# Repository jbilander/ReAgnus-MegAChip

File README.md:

# ReAgnus-MegAChip
A ReAgnus MegaAChip PCB that takes a Gowin FPGA with embedded PSRAM, a PLCC-84 plug and FET level shifters.

***

THIS IS WORK IN PROGRESS, HARDWARE IS VERIFIED WORKING. FIRMWARE YET TO BE DEVELOPED. BUILD AT YOUR OWN RISK.

***

***

<br />

***

***

For hi-res pics goto the hi-res folder in pics
https://github.com/jbilander/ReAgnus-MegAChip/tree/main/pics/hi-res

***

BOM Rev. 2C
---------
Designator  | Name/Value   | Package | Notes
-|-|-|-|
U1 | Gowin FPGA GW1NR-UV9LQ144PC6/I5 | LQFP-144 | FPGA - Field Programmable Gate Array, 8640 LE, 121 I/O, Embedded 64Mbit 16-bit PSRAM <br /> [GW1NR-UV9LQ144PC6/I5](https://www.mouser.com/ProductDetail/192-1NRUV9LQ144PC6I5)
U2 | Voltage Regulator 3.3V, <br /> LM1117-3.3 or <br /> AMS1117-3.3 | SOT-223 | 3.3V 1A Low Drop-Out (LDO) Voltage regulator. https://www.aliexpress.com/item/32869037691.html
U3 | Voltage Regulator 4.3V, TPS73643DBVR or <br /> ABLIC S-1132B43-M5T1U | SOT-23-5 | 4.3V LDO Voltage Regulator<br />[TPS73643DBVR](https://www.mouser.com/ProductDetail/595-TPS73643DBVR) <br />[S-1132B43-M5T1U](https://www.mouser.com/ProductDetail/628-S-1132B43-M5T1G)
U4,U5,U6,U7 | Digital Bus Switch ICs 20-Bit FET, SN74CBT16210CDGVR | TVSOP-48 | FET Level-shifter <br /> [SN74CBT16210CDGVR](https://www.mouser.com/ProductDetail/595-SN74CBT16210CDGV)
U8 | 74LVC1G07 Single Buffer With Open-Drain Output | SOT-353, SC-70-5 | [74LVC1G07](https://www.mouser.com/ProductDetail/621-74LVC1G07SE-7)
U9 | X-tal driver 74LVC1GX04  | TSOP-6 1.65x3.05mm P0.95mm | [74LVC1GX04](https://www.mouser.com/ProductDetail/771-LVC1GX04GV125)
U10 | Bus Transceiver 74LVC245APW,118 | TSSOP-20 | [74LVC245APW-T](https://www.mouser.com/ProductDetail/771-74LVC245APW-T)
U11 | Voltage Regulator 1.8V, <br /> MCP1702T-1802E/CB | SOT-23 | 1.8V Low Drop-Out (LDO) Voltage regulator. [MCP1702T1802E-CB](https://www.mouser.com/ProductDetail/579-MCP1702T1802E-CB)
U12 | Winslow PLCC-84 Plug | PLCC-84 Plug | Optionally homemade plug
U13 | PLCC-84_TH_pin_holes | Agnus_TH_plug_pins | Pins to use with homemade plug, 1.27mm pitch Long Pin 1x40P or 1x50P [Aliexpress](https://www.aliexpress.com/item/32894911767.html) Cut to length after soldering.
Y1 | 18pF Crystal 28.6363 MHz (NTSC) or 28.375 MHz (PAL) | 3.2 mm x 2.5 mm | [ECS-286.3-18-33-JEM-TR](https://www.mouser.com/ProductDetail/520-286.3-18-33-JEMT) (NTSC)<br /> [ABM8-28.375MHZ-B2-T](https://www.mouser.com/ProductDetail/815-ABM8-28.375-B2-T) (PAL)
R1 | Resistor 1k Ω | 0603 | Resistor in optional Oscillator-circuit
R2 | Resistor 2.2M Ω | 0603 | Resistor in optional Oscillator-circuit
R3 | Resistor 33 Ω | 0603 | Series resistor for CLK from U9 to avoid reflections (in optional Oscillator-circuit).
R4 | Resistor 10k Ω | 0603 | Pull-up resistor for pin 41 (PAL/NTSC-selector for A500 Rev.6A/A2000/A3000-pinout) since A500 Rev.6A doesn't have pull-up on motherboard like A2000/A3000/A3000T have. Only needed for A500 Rev.6A. but doesn't hurt to populate anyway. 
R5 | Resistor 4.7k Ω | 0603 | Pull-down resistor for TCK in JTAG.
RN1 | 4.7k or 10k Ω RES ARRAY 4 Resistors | 1206 | [CAY16-4701F4LF](https://www.mouser.com/ProductDetail/652-CAY16A-4701F4LF) or [CAY16-103J4LF](https://www.mouser.com/ProductDetail/652-CAY16-103J4LF)
RN2 | 4.7k (CAY16-4701F4LF) RES ARRAY 4 Resistors | 1206 | [CAY16-4701F4LF](https://www.mouser.com/ProductDetail/652-CAY16A-4701F4LF)
C1 | Capacitor Radial Polarized 100uF | 2.5mm pitch, Through-Hole | [ECE-A0JKA101I](https://www.mouser.com/ProductDetail/667-ECE-A0JKA101I)
C2-C4 | Capacitor 10uF | 1206 | 
C5 | Capacitor 1uF | 0805 | 
C6 | Capacitor 10uF | 0805 |
C9 | Capacitor 1uF | 0805 |
C7,C8,C10-C16 | Capacitor 0.1uF = 100nF | 0805 |
C17-C19 | Capacitor 0.01uF = 10nF | 0805 (or 0603) |
C20 | Capacitor 0.1uF = 100nF | 0603 | Decoupling cap for U8
C21-C24 | Capacitor 0.1uF = 100nF | 0603 | Decoupling caps for U4-U7
C25 | Capacitor 0.1uF = 100nF | 0603 | Optional cap for U3, NR (Noise Reduction) pin 4 on TPS73643DBVR, this pin is NC on ABLIC S-1200B43-M5T1U
C26 | Capacitor 0.01uF = 10nF | 0603 |
C27-C28 | Capacitor 0.1uF = 100nF | 0603 |
C29-C30 | Multilayer Ceramic Capacitors MLCC - 32pF | 0603 | [06031A320FAT2A ](https://www.mouser.com/ProductDetail/581-06031A320FAT2A) Caps for optional oscillator circuit 
L1 | (Ferrite Bead 600ohms 100MHz .5A Monolithic) or 0 Ω resistor  | 0805 | [HZ0805E601R-10](https://www.mouser.com/ProductDetail/875-HZ0805E601R-10) or 0 Ω resistor 
J1 | VCC/GND Power Header Male | TH 1 x 2 Pin, 2.54mm pitch | For external power supply to allow programming of device when not plugged into the Amiga socket.
J2 | JTAG Pin Header Male | TH 2 x 5 Pin, 2.54mm pitch|
J3 | A20-A23 Pin Header Male | TH 2 x 2 Pin, 2.00mm pitch | Input Address lines for jumper-wires A20-A23
J4 | GND MountingHole_2.2mm_M2_Pad_Via | nut and bolt M2 size | for solid grounding via a ring lug connector and a thick jumper wire to Motherboard

***

Select one of the crystals 28.375 MHz (PAL) or 28.6363 MHz for the optional onboard oscillator circuit. Probably you want to select PAL/NTSC opposite to what your CLK on motherboard has, this in order to be able to switch between native PAL/NTSC with only a JP-setting on the MegaChip board.
***

***

***

***

***

***

***

***

***

***

***

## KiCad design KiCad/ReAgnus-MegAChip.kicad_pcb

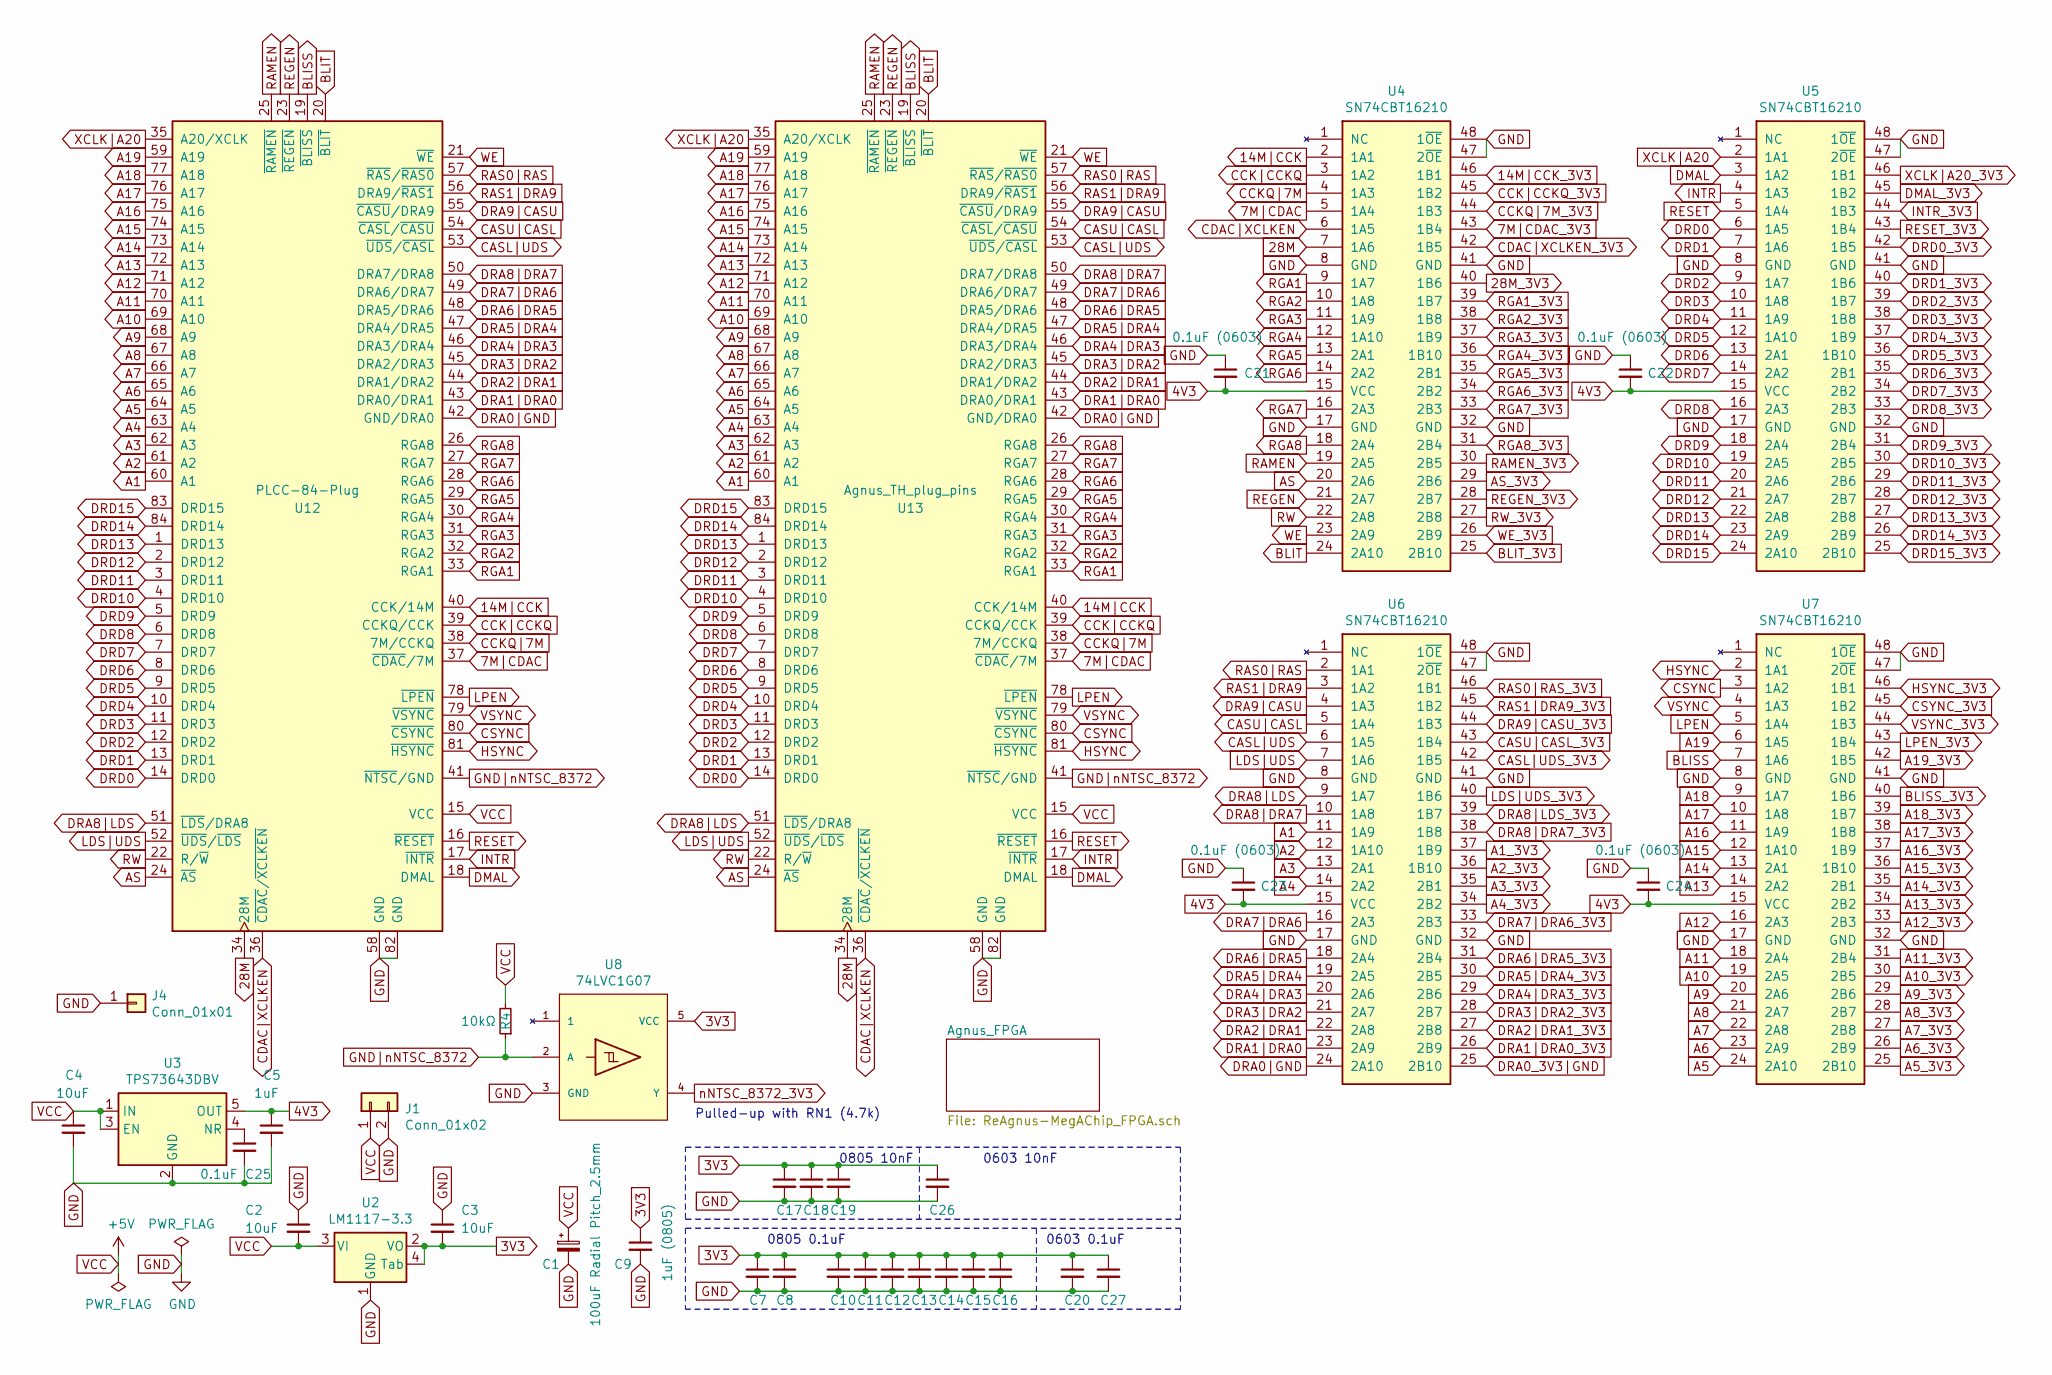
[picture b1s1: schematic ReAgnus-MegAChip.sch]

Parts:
C1: 100uF Radial Pitch_2.5mm; CP_Radial_D5.0mm_P2.50mm
C2, C3: 10uF; C_1206_3216Metric_Pad1.42x1.75mm_HandSolder
C4: 10uF; C_1206_3216Metric_Pad1.33x1.80mm_HandSolder
C5: 1uF; C_0805_2012Metric_Pad1.18x1.45mm_HandSolder
C7, C8, C10, C11, C12, C13, C14, C15, C16: 0.1uF; C_0805_2012Metric_Pad1.15x1.40mm_HandSolder
C9: 1uF (0805); C_0805_2012Metric_Pad1.15x1.40mm_HandSolder
C17, C18, C19: 0.01uF; C_0805_2012Metric_Pad1.15x1.40mm_HandSolder
C20, C26: 0.01uF; C_0603_1608Metric_Pad1.05x0.95mm_HandSolder
C21, C22, C23, C24: 0.1uF (0603); C_0603_1608Metric_Pad1.05x0.95mm_HandSolder
C25, C27: 0.1uF; C_0603_1608Metric_Pad1.08x0.95mm_HandSolder
J1: Conn_01x02; PinHeader_1x02_P2.54mm_Vertical
J4: Conn_01x01; MountingHole_2.2mm_M2_Pad_Via
R4: 10kΩ; R_0603_1608Metric_Pad0.98x0.95mm_HandSolder
U2: LM1117-3.3; SOT-223
U3: TPS73643DBV; SOT-23-5
U4, U5, U6, U7: SN74CBT16210; TSSOP-48_4.4x9.7mm_P0.4mm
U8: 74LVC1G07; SOT-353_SC-70-5_Custom_Handsoldering
U12: PLCC-84-Plug; PLCC-84_Plug_P1.27mm_mirrored
U13: Agnus_TH_plug_pins; PLCC-84_TH_pin_holes

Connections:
3V3: C3.2, C7.1, C8.1, C9.1, C10.1, C11.1, C12.1, C13.1, C14.1, C15.1, C16.1, C17.1, C18.1, C19.1, C20.1, C26.1, C27.1, U2.2 (VO), U2.4 (Tab), U8.5 (VCC); also elsewhere on the board
4V3: C5.1, C21.2, C22.2, C23.2, C24.2, U3.5 (OUT), U4.15 (VCC), U5.15 (VCC), U6.15 (VCC), U7.15 (VCC)
7M|CDAC: U4.5 (1A4), U12.37 (~CDAC~/7M), U13.37 (~CDAC~/7M)
7M|CDAC_3V3: U4.43 (1B4); also elsewhere on the board
14M|CCK: U4.2 (1A1), U12.40 (CCK/14M), U13.40 (CCK/14M)
14M|CCK_3V3: U4.46 (1B1); also elsewhere on the board
28M: U4.7 (1A6), U12.34 (28M), U13.34 (28M)
28M_3V3: U4.40 (1B6); also elsewhere on the board
A1: U6.11 (1A9), U12.60 (A1), U13.60 (A1)
A1_3V3: U6.37 (1B9); also elsewhere on the board
A2: U6.12 (1A10), U12.61 (A2), U13.61 (A2)
A2_3V3: U6.36 (1B10); also elsewhere on the board
A3: U6.13 (2A1), U12.62 (A3), U13.62 (A3)
A3_3V3: U6.35 (2B1); also elsewhere on the board
A4: U6.14 (2A2), U12.63 (A4), U13.63 (A4)
A4_3V3: U6.34 (2B2); also elsewhere on the board
A5: U7.24 (2A10), U12.64 (A5), U13.64 (A5)
A5_3V3: U7.25 (2B10); also elsewhere on the board
A6: U7.23 (2A9), U12.65 (A6), U13.65 (A6)
A6_3V3: U7.26 (2B9); also elsewhere on the board
A7: U7.22 (2A8), U12.66 (A7), U13.66 (A7)
A7_3V3: U7.27 (2B8); also elsewhere on the board
A8: U7.21 (2A7), U12.67 (A8), U13.67 (A8)
A8_3V3: U7.28 (2B7); also elsewhere on the board
A9: U7.20 (2A6), U12.68 (A9), U13.68 (A9)
A9_3V3: U7.29 (2B6); also elsewhere on the board
A10: U7.19 (2A5), U12.69 (A10), U13.69 (A10)
A10_3V3: U7.30 (2B5); also elsewhere on the board
A11: U7.18 (2A4), U12.70 (A11), U13.70 (A11)
A11_3V3: U7.31 (2B4); also elsewhere on the board
A12: U7.16 (2A3), U12.71 (A12), U13.71 (A12)
A12_3V3: U7.33 (2B3); also elsewhere on the board
A13: U7.14 (2A2), U12.72 (A13), U13.72 (A13)
A13_3V3: U7.34 (2B2); also elsewhere on the board
A14: U7.13 (2A1), U12.73 (A14), U13.73 (A14)
A14_3V3: U7.35 (2B1); also elsewhere on the board
A15: U7.12 (1A10), U12.74 (A15), U13.74 (A15)
A15_3V3: U7.36 (1B10); also elsewhere on the board
A16: U7.11 (1A9), U12.75 (A16), U13.75 (A16)
A16_3V3: U7.37 (1B9); also elsewhere on the board
A17: U7.10 (1A8), U12.76 (A17), U13.76 (A17)
A17_3V3: U7.38 (1B8); also elsewhere on the board
A18: U7.9 (1A7), U12.77 (A18), U13.77 (A18)
A18_3V3: U7.39 (1B7); also elsewhere on the board
A19: U7.6 (1A5), U12.59 (A19), U13.59 (A19)
A19_3V3: U7.42 (1B5); also elsewhere on the board
AS: U4.20 (2A6), U12.24 (~AS), U13.24 (~AS)
AS_3V3: U4.29 (2B6); also elsewhere on the board
BLISS: U7.7 (1A6), U12.19 (~BLISS), U13.19 (~BLISS)
BLISS_3V3: U7.40 (1B6); also elsewhere on the board
BLIT: U4.24 (2A10), U12.20 (~BLIT), U13.20 (~BLIT)
BLIT_3V3: U4.25 (2B10); also elsewhere on the board
CASL|UDS: U6.6 (1A5), U12.53 (~UDS~/~CASL), U13.53 (~UDS~/~CASL)
CASL|UDS_3V3: U6.42 (1B5); also elsewhere on the board
CASU|CASL: U6.5 (1A4), U12.54 (~CASL~/~CASU), U13.54 (~CASL~/~CASU)
CASU|CASL_3V3: U6.43 (1B4); also elsewhere on the board
CCKQ|7M: U4.4 (1A3), U12.38 (7M/CCKQ), U13.38 (7M/CCKQ)
CCKQ|7M_3V3: U4.44 (1B3); also elsewhere on the board
CCK|CCKQ: U4.3 (1A2), U12.39 (CCKQ/CCK), U13.39 (CCKQ/CCK)
CCK|CCKQ_3V3: U4.45 (1B2); also elsewhere on the board
CDAC|XCLKEN: U4.6 (1A5), U12.36 (~CDAC~/~XCLKEN), U13.36 (~CDAC~/~XCLKEN)
CDAC|XCLKEN_3V3: U4.42 (1B5); also elsewhere on the board
CSYNC: U7.3 (1A2), U12.80 (~CSYNC), U13.80 (~CSYNC)
CSYNC_3V3: U7.45 (1B2); also elsewhere on the board
DMAL: U5.3 (1A2), U12.18 (DMAL), U13.18 (DMAL)
DMAL_3V3: U5.45 (1B2); also elsewhere on the board
DRA0_3V3|GND: U6.25 (2B10); also elsewhere on the board
DRA0|GND: U6.24 (2A10), U12.42 (GND/DRA0), U13.42 (GND/DRA0)
DRA1|DRA0: U6.23 (2A9), U12.43 (DRA0/DRA1), U13.43 (DRA0/DRA1)
DRA1|DRA0_3V3: U6.26 (2B9); also elsewhere on the board
DRA2|DRA1: U6.22 (2A8), U12.44 (DRA1/DRA2), U13.44 (DRA1/DRA2)
DRA2|DRA1_3V3: U6.27 (2B8); also elsewhere on the board
DRA3|DRA2: U6.21 (2A7), U12.45 (DRA2/DRA3), U13.45 (DRA2/DRA3)
DRA3|DRA2_3V3: U6.28 (2B7); also elsewhere on the board
DRA4|DRA3: U6.20 (2A6), U12.46 (DRA3/DRA4), U13.46 (DRA3/DRA4)
DRA4|DRA3_3V3: U6.29 (2B6); also elsewhere on the board
DRA5|DRA4: U6.19 (2A5), U12.47 (DRA4/DRA5), U13.47 (DRA4/DRA5)
DRA5|DRA4_3V3: U6.30 (2B5); also elsewhere on the board
DRA6|DRA5: U6.18 (2A4), U12.48 (DRA5/DRA6), U13.48 (DRA5/DRA6)
DRA6|DRA5_3V3: U6.31 (2B4); also elsewhere on the board
DRA7|DRA6: U6.16 (2A3), U12.49 (DRA6/DRA7), U13.49 (DRA6/DRA7)
DRA7|DRA6_3V3: U6.33 (2B3); also elsewhere on the board
DRA8|DRA7: U6.10 (1A8), U12.50 (DRA7/DRA8), U13.50 (DRA7/DRA8)
DRA8|DRA7_3V3: U6.38 (1B8); also elsewhere on the board
DRA8|LDS: U6.9 (1A7), U12.51 (~LDS~/DRA8), U13.51 (~LDS~/DRA8)
DRA8|LDS_3V3: U6.39 (1B7); also elsewhere on the board
DRA9|CASU: U6.4 (1A3), U12.55 (~CASU~/DRA9), U13.55 (~CASU~/DRA9)
DRA9|CASU_3V3: U6.44 (1B3); also elsewhere on the board
DRD0: U5.6 (1A5), U12.14 (DRD0), U13.14 (DRD0)
DRD0_3V3: U5.42 (1B5); also elsewhere on the board
DRD1: U5.7 (1A6), U12.13 (DRD1), U13.13 (DRD1)
DRD1_3V3: U5.40 (1B6); also elsewhere on the board
DRD2: U5.9 (1A7), U12.12 (DRD2), U13.12 (DRD2)
DRD2_3V3: U5.39 (1B7); also elsewhere on the board
DRD3: U5.10 (1A8), U12.11 (DRD3), U13.11 (DRD3)
DRD3_3V3: U5.38 (1B8); also elsewhere on the board
DRD4: U5.11 (1A9), U12.10 (DRD4), U13.10 (DRD4)
DRD4_3V3: U5.37 (1B9); also elsewhere on the board
DRD5: U5.12 (1A10), U12.9 (DRD5), U13.9 (DRD5)
DRD5_3V3: U5.36 (1B10); also elsewhere on the board
DRD6: U5.13 (2A1), U12.8 (DRD6), U13.8 (DRD6)
DRD6_3V3: U5.35 (2B1); also elsewhere on the board
DRD7: U5.14 (2A2), U12.7 (DRD7), U13.7 (DRD7)
DRD7_3V3: U5.34 (2B2); also elsewhere on the board
DRD8: U5.16 (2A3), U12.6 (DRD8), U13.6 (DRD8)
DRD8_3V3: U5.33 (2B3); also elsewhere on the board
DRD9: U5.18 (2A4), U12.5 (DRD9), U13.5 (DRD9)
DRD9_3V3: U5.31 (2B4); also elsewhere on the board
DRD10: U5.19 (2A5), U12.4 (DRD10), U13.4 (DRD10)
DRD10_3V3: U5.30 (2B5); also elsewhere on the board
DRD11: U5.20 (2A6), U12.3 (DRD11), U13.3 (DRD11)
DRD11_3V3: U5.29 (2B6); also elsewhere on the board
DRD12: U5.21 (2A7), U12.2 (DRD12), U13.2 (DRD12)
DRD12_3V3: U5.28 (2B7); also elsewhere on the board
DRD13: U5.22 (2A8), U12.1 (DRD13), U13.1 (DRD13)
DRD13_3V3: U5.27 (2B8); also elsewhere on the board
DRD14: U5.23 (2A9), U12.84 (DRD14), U13.84 (DRD14)
DRD14_3V3: U5.26 (2B9); also elsewhere on the board
DRD15: U5.24 (2A10), U12.83 (DRD15), U13.83 (DRD15)
DRD15_3V3: U5.25 (2B10); also elsewhere on the board
GND: C1.2, C2.1, C3.1, C4.2, C5.2, C7.2, C8.2, C9.2, C10.2, C11.2, C12.2, C13.2, C14.2, C15.2, C16.2, C17.2, C18.2, C19.2, C20.2, C21.1, C22.1, C23.1, C24.1, C25.2, C26.2, C27.2, J1.2, J4.1, U2.1 (GND), U3.2 (GND), U4.8 (GND), U4.17 (GND), U4.32 (GND), U4.41 (GND), U4.47 (2~OE), U4.48 (1~OE), U5.8 (GND), U5.17 (GND), U5.32 (GND), U5.41 (GND), U5.47 (2~OE), U5.48 (1~OE), U6.8 (GND), U6.17 (GND), U6.32 (GND), U6.41 (GND), U6.47 (2~OE), U6.48 (1~OE), U7.8 (GND), U7.17 (GND), U7.32 (GND), U7.41 (GND), U7.47 (2~OE), U7.48 (1~OE), U8.3 (GND), U12.58 (GND), U12.82 (GND), U13.58 (GND), U13.82 (GND); also elsewhere on the board
GND|nNTSC_8372: R4.1, U8.2 (A), U12.41 (~NTSC~/GND), U13.41 (~NTSC~/GND)
HSYNC: U7.2 (1A1), U12.81 (~HSYNC), U13.81 (~HSYNC)
HSYNC_3V3: U7.46 (1B1); also elsewhere on the board
INTR: U5.4 (1A3), U12.17 (~INTR), U13.17 (~INTR)
INTR_3V3: U5.44 (1B3); also elsewhere on the board
LDS|UDS: U6.7 (1A6), U12.52 (~UDS~/~LDS~), U13.52 (~UDS~/~LDS~)
LDS|UDS_3V3: U6.40 (1B6); also elsewhere on the board
LPEN: U7.5 (1A4), U12.78 (~LPEN), U13.78 (~LPEN)
LPEN_3V3: U7.43 (1B4); also elsewhere on the board
unnamed: C25.1, U3.4 (NR)
RAMEN: U4.19 (2A5), U12.25 (~RAMEN), U13.25 (~RAMEN)
RAMEN_3V3: U4.30 (2B5); also elsewhere on the board
RAS0|RAS: U6.2 (1A1), U12.57 (~RAS~/~RAS0), U13.57 (~RAS~/~RAS0)
RAS0|RAS_3V3: U6.46 (1B1); also elsewhere on the board
RAS1|DRA9: U6.3 (1A2), U12.56 (DRA9/~RAS1), U13.56 (DRA9/~RAS1)
RAS1|DRA9_3V3: U6.45 (1B2); also elsewhere on the board
REGEN: U4.21 (2A7), U12.23 (~REGEN), U13.23 (~REGEN)
REGEN_3V3: U4.28 (2B7); also elsewhere on the board
RESET: U5.5 (1A4), U12.16 (~RESET), U13.16 (~RESET)
RESET_3V3: U5.43 (1B4); also elsewhere on the board
RGA1: U4.9 (1A7), U12.33 (RGA1), U13.33 (RGA1)
RGA1_3V3: U4.39 (1B7); also elsewhere on the board
RGA2: U4.10 (1A8), U12.32 (RGA2), U13.32 (RGA2)
RGA2_3V3: U4.38 (1B8); also elsewhere on the board
RGA3: U4.11 (1A9), U12.31 (RGA3), U13.31 (RGA3)
RGA3_3V3: U4.37 (1B9); also elsewhere on the board
RGA4: U4.12 (1A10), U12.30 (RGA4), U13.30 (RGA4)
RGA4_3V3: U4.36 (1B10); also elsewhere on the board
RGA5: U4.13 (2A1), U12.29 (RGA5), U13.29 (RGA5)
RGA5_3V3: U4.35 (2B1); also elsewhere on the board
RGA6: U4.14 (2A2), U12.28 (RGA6), U13.28 (RGA6)
RGA6_3V3: U4.34 (2B2); also elsewhere on the board
RGA7: U4.16 (2A3), U12.27 (RGA7), U13.27 (RGA7)
RGA7_3V3: U4.33 (2B3); also elsewhere on the board
RGA8: U4.18 (2A4), U12.26 (RGA8), U13.26 (RGA8)
RGA8_3V3: U4.31 (2B4); also elsewhere on the board
RW: U4.22 (2A8), U12.22 (R/~W), U13.22 (R/~W)
RW_3V3: U4.27 (2B8); also elsewhere on the board
VCC: C1.1, C2.2, C4.1, J1.1, R4.2, U2.3 (VI), U3.1 (IN), U3.3 (EN), U12.15 (VCC), U13.15 (VCC)
VSYNC: U7.4 (1A3), U12.79 (~VSYNC), U13.79 (~VSYNC)
VSYNC_3V3: U7.44 (1B3); also elsewhere on the board
WE: U4.23 (2A9), U12.21 (~WE), U13.21 (~WE)
WE_3V3: U4.26 (2B9); also elsewhere on the board
XCLK|A20: U5.2 (1A1), U12.35 (A20/XCLK), U13.35 (A20/XCLK)
XCLK|A20_3V3: U5.46 (1B1); also elsewhere on the board
nNTSC_8372_3V3: U8.4 (Y); also elsewhere on the board

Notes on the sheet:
Pulled-up with RN1 (4.7k)
0805 10nF
0805 0.1uF
0603 10nF
0603 0.1uF

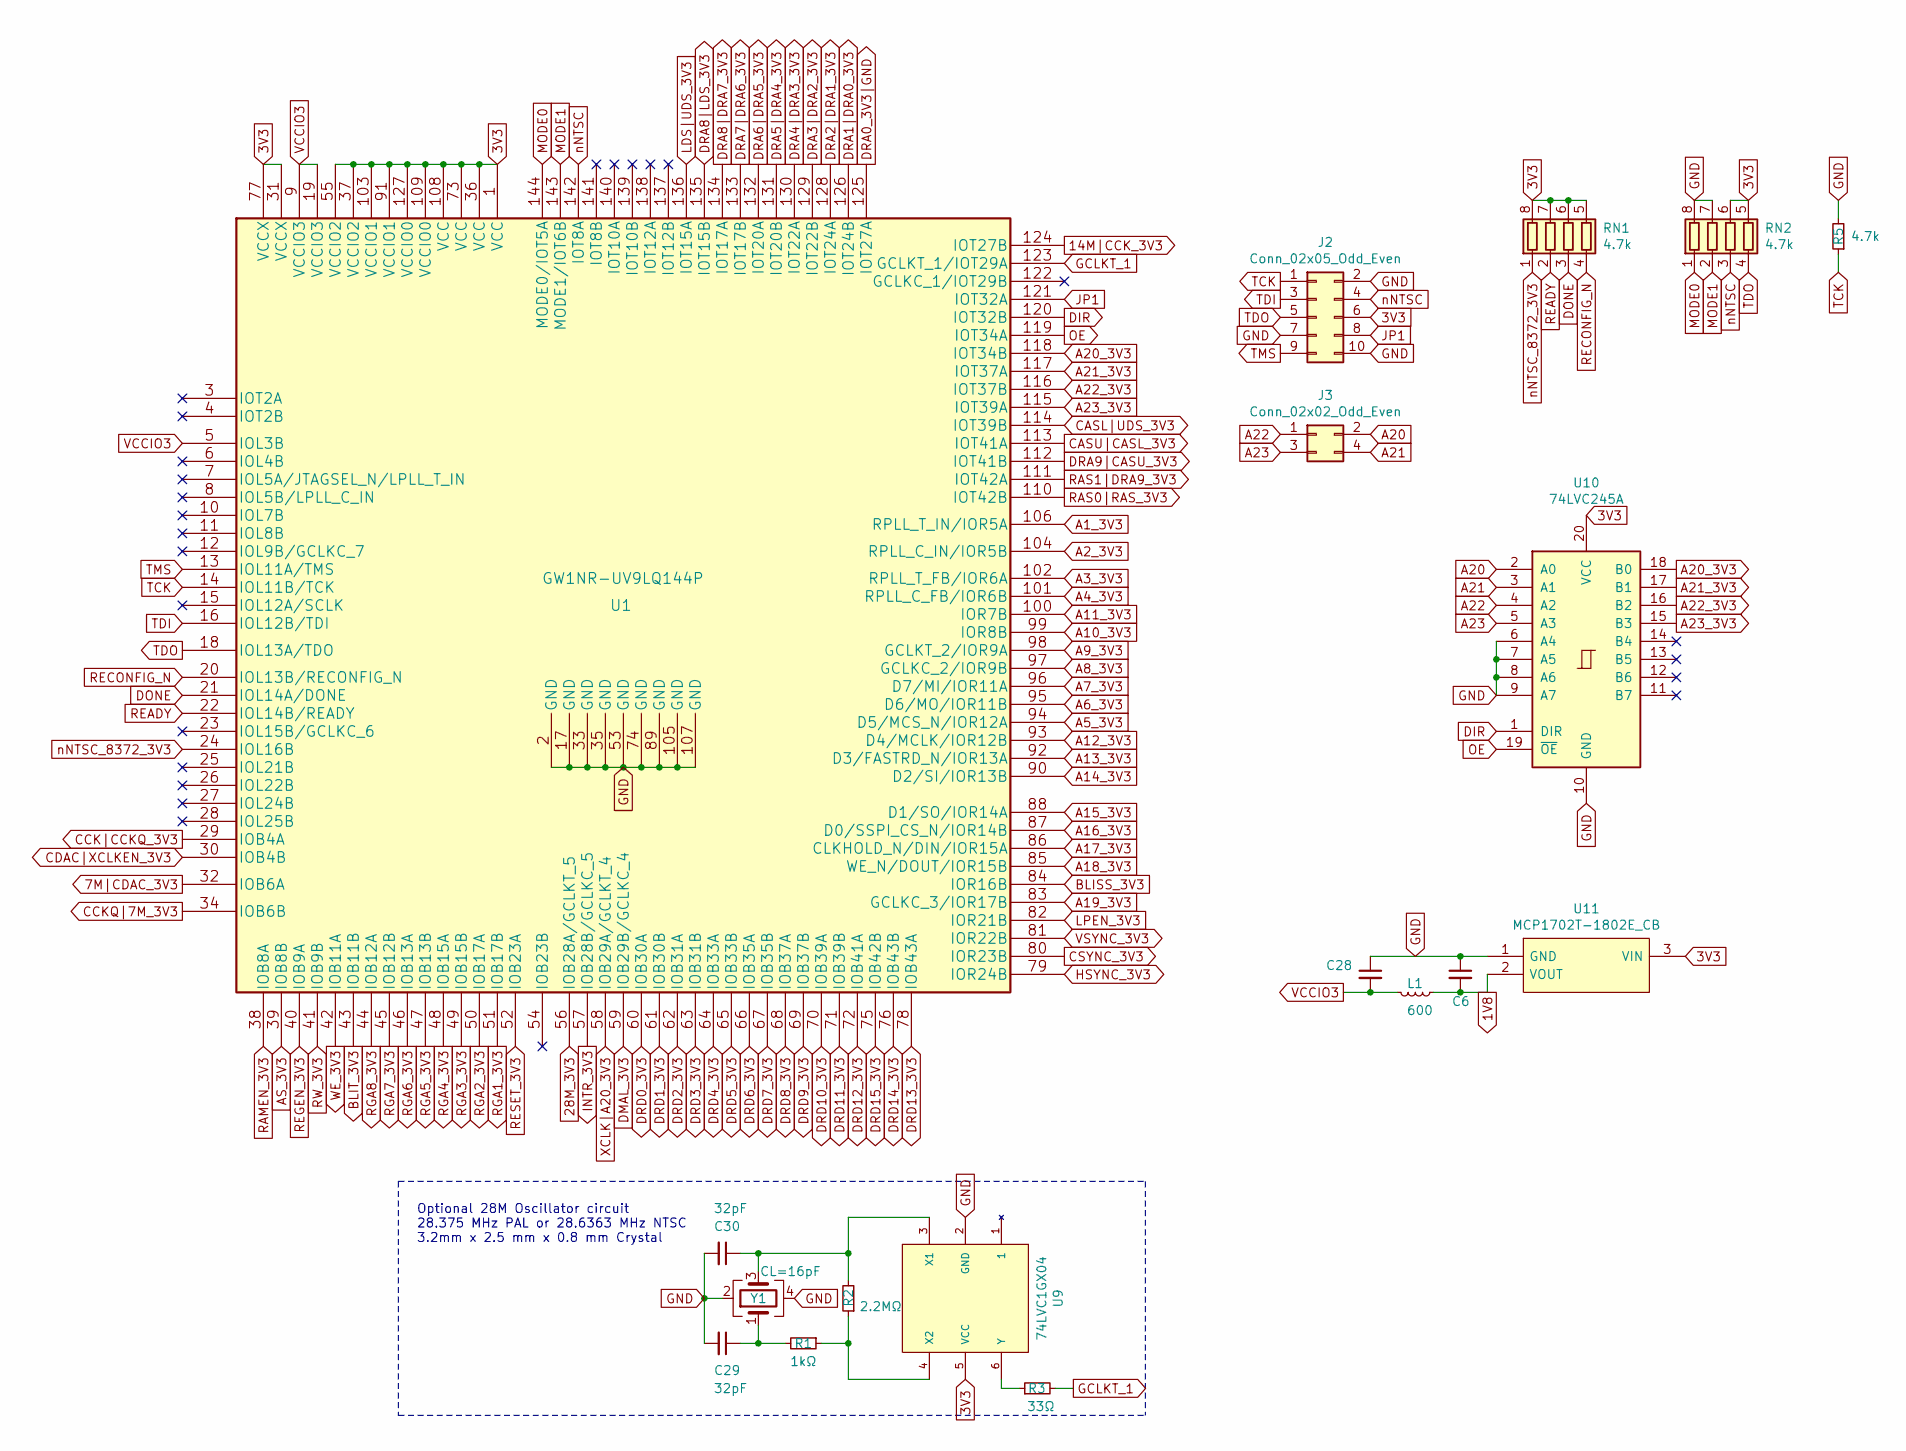
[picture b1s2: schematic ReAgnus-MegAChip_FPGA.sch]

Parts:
C6: 10uF; C_0805_2012Metric_Pad1.18x1.45mm_HandSolder
C28: 0.1uF; C_0603_1608Metric_Pad1.08x0.95mm_HandSolder
C29, C30: 32pF; C_0603_1608Metric_Pad1.05x0.95mm_HandSolder
J2: Conn_02x05_Odd_Even; PinHeader_2x05_P2.54mm_Vertical
J3: Conn_02x02_Odd_Even; PinHeader_2x02_P2.00mm_Vertical
L1: 600; L_0805_2012Metric_Pad1.05x1.20mm_HandSolder
R1: 1kΩ; R_0603_1608Metric_Pad1.05x0.95mm_HandSolder
R2: 2.2MΩ; R_0603_1608Metric_Pad1.05x0.95mm_HandSolder
R3: 33Ω; R_0603_1608Metric_Pad0.98x0.95mm_HandSolder
R5: 4.7k; R_0603_1608Metric_Pad0.98x0.95mm_HandSolder
RN1, RN2: 4.7k; RESCAF80P320X160X60-8N
U1: GW1NR-UV9LQ144P; LQFP-144_20x20mm_P0.5mm
U9: 74LVC1GX04; TSOP-6_1.65x3.05mm_P0.95mm
U10: 74LVC245A; TSSOP-20_4.4x6.5mm_P0.65mm
U11: MCP1702T-1802E_CB; SOT-23_Handsoldering
Y1: CL=16pF; Crystal_SMD_SeikoEpson_FA238-4Pin_3.2x2.5mm

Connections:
1V8: C6.2, L1.1, U11.2 (VOUT)
3V3: J2.6, RN1.5 (R4.2), RN1.6 (R3.2), RN1.7 (R2.2), RN1.8 (R1.2), RN2.5 (R4.2), RN2.6 (R3.2), U1.1 (VCC), U1.31 (VCCX), U1.36 (VCC), U1.37 (VCCIO2), U1.55 (VCCIO2), U1.73 (VCC), U1.77 (VCCX), U1.91 (VCCIO1), U1.103 (VCCIO1), U1.108 (VCC), U1.109 (VCCIO0), U1.127 (VCCIO0), U9.5 (VCC), U10.20 (VCC), U11.3 (VIN); also elsewhere on the board
7M|CDAC_3V3: U1.32 (IOB6A); also elsewhere on the board
14M|CCK_3V3: U1.124 (IOT27B); also elsewhere on the board
28M_3V3: U1.56 (IOB28A/GCLKT_5); also elsewhere on the board
A1_3V3: U1.106 (RPLL_T_IN/IOR5A); also elsewhere on the board
A2_3V3: U1.104 (RPLL_C_IN/IOR5B); also elsewhere on the board
A3_3V3: U1.102 (RPLL_T_FB/IOR6A); also elsewhere on the board
A4_3V3: U1.101 (RPLL_C_FB/IOR6B); also elsewhere on the board
A5_3V3: U1.94 (D5/MCS_N/IOR12A); also elsewhere on the board
A6_3V3: U1.95 (D6/MO/IOR11B); also elsewhere on the board
A7_3V3: U1.96 (D7/MI/IOR11A); also elsewhere on the board
A8_3V3: U1.97 (GCLKC_2/IOR9B); also elsewhere on the board
A9_3V3: U1.98 (GCLKT_2/IOR9A); also elsewhere on the board
A10_3V3: U1.99 (IOR8B); also elsewhere on the board
A11_3V3: U1.100 (IOR7B); also elsewhere on the board
A12_3V3: U1.93 (D4/MCLK/IOR12B); also elsewhere on the board
A13_3V3: U1.92 (D3/FASTRD_N/IOR13A); also elsewhere on the board
A14_3V3: U1.90 (D2/SI/IOR13B); also elsewhere on the board
A15_3V3: U1.88 (D1/SO/IOR14A); also elsewhere on the board
A16_3V3: U1.87 (D0/SSPI_CS_N/IOR14B); also elsewhere on the board
A17_3V3: U1.86 (CLKHOLD_N/DIN/IOR15A); also elsewhere on the board
A18_3V3: U1.85 (WE_N/DOUT/IOR15B); also elsewhere on the board
A19_3V3: U1.83 (GCLKC_3/IOR17B); also elsewhere on the board
A20: J3.2, U10.2 (A0)
A20_3V3: U1.118 (IOT34B), U10.18 (B0)
A21: J3.4, U10.3 (A1)
A21_3V3: U1.117 (IOT37A), U10.17 (B1)
A22: J3.1, U10.4 (A2)
A22_3V3: U1.116 (IOT37B), U10.16 (B2)
A23: J3.3, U10.5 (A3)
A23_3V3: U1.115 (IOT39A), U10.15 (B3)
AS_3V3: U1.39 (IOB8B); also elsewhere on the board
BLISS_3V3: U1.84 (IOR16B); also elsewhere on the board
BLIT_3V3: U1.43 (IOB11B); also elsewhere on the board
CASL|UDS_3V3: U1.114 (IOT39B); also elsewhere on the board
CASU|CASL_3V3: U1.113 (IOT41A); also elsewhere on the board
CCKQ|7M_3V3: U1.34 (IOB6B); also elsewhere on the board
CCK|CCKQ_3V3: U1.29 (IOB4A); also elsewhere on the board
CDAC|XCLKEN_3V3: U1.30 (IOB4B); also elsewhere on the board
CSYNC_3V3: U1.80 (IOR23B); also elsewhere on the board
DIR: U1.120 (IOT32B), U10.1 (DIR)
DMAL_3V3: U1.59 (IOB29B/GCLKC_4); also elsewhere on the board
DONE: RN1.3 (R3.1), U1.21 (IOL14A/DONE)
DRA0_3V3|GND: U1.125 (IOT27A); also elsewhere on the board
DRA1|DRA0_3V3: U1.126 (IOT24B); also elsewhere on the board
DRA2|DRA1_3V3: U1.128 (IOT24A); also elsewhere on the board
DRA3|DRA2_3V3: U1.129 (IOT22B); also elsewhere on the board
DRA4|DRA3_3V3: U1.130 (IOT22A); also elsewhere on the board
DRA5|DRA4_3V3: U1.131 (IOT20B); also elsewhere on the board
DRA6|DRA5_3V3: U1.132 (IOT20A); also elsewhere on the board
DRA7|DRA6_3V3: U1.133 (IOT17B); also elsewhere on the board
DRA8|DRA7_3V3: U1.134 (IOT17A); also elsewhere on the board
DRA8|LDS_3V3: U1.135 (IOT15B); also elsewhere on the board
DRA9|CASU_3V3: U1.112 (IOT41B); also elsewhere on the board
DRD0_3V3: U1.60 (IOB30A); also elsewhere on the board
DRD1_3V3: U1.61 (IOB30B); also elsewhere on the board
DRD2_3V3: U1.62 (IOB31A); also elsewhere on the board
DRD3_3V3: U1.63 (IOB31B); also elsewhere on the board
DRD4_3V3: U1.64 (IOB33A); also elsewhere on the board
DRD5_3V3: U1.65 (IOB33B); also elsewhere on the board
DRD6_3V3: U1.66 (IOB35A); also elsewhere on the board
DRD7_3V3: U1.67 (IOB35B); also elsewhere on the board
DRD8_3V3: U1.68 (IOB37A); also elsewhere on the board
DRD9_3V3: U1.69 (IOB37B); also elsewhere on the board
DRD10_3V3: U1.70 (IOB39A); also elsewhere on the board
DRD11_3V3: U1.71 (IOB39B); also elsewhere on the board
DRD12_3V3: U1.72 (IOB41A); also elsewhere on the board
DRD13_3V3: U1.78 (IOB43A); also elsewhere on the board
DRD14_3V3: U1.76 (IOB43B); also elsewhere on the board
DRD15_3V3: U1.75 (IOB42B); also elsewhere on the board
GCLKT_1: R3.2, U1.123 (GCLKT_1/IOT29A)
GND: C6.1, C28.1, C29.2, C30.2, J2.2, J2.7, J2.10, R5.2, RN2.7 (R2.2), RN2.8 (R1.2), U1.2 (GND), U1.17 (GND), U1.33 (GND), U1.35 (GND), U1.53 (GND), U1.74 (GND), U1.89 (GND), U1.105 (GND), U1.107 (GND), U9.2 (GND), U10.6 (A4), U10.7 (A5), U10.8 (A6), U10.9 (A7), U10.10 (GND), U11.1 (GND), Y1.2, Y1.4; also elsewhere on the board
HSYNC_3V3: U1.79 (IOR24B); also elsewhere on the board
INTR_3V3: U1.57 (IOB28B/GCLKC_5); also elsewhere on the board
JP1: J2.8, U1.121 (IOT32A)
LDS|UDS_3V3: U1.136 (IOT15A); also elsewhere on the board
LPEN_3V3: U1.82 (IOR21B); also elsewhere on the board
MODE0: RN2.1 (R1.1), U1.144 (MODE0/IOT5A)
MODE1: RN2.2 (R2.1), U1.143 (MODE1/IOT6B)
unnamed: C29.1, R1.2, Y1.1
unnamed: C30.1, R2.2, U9.3 (X1), Y1.3
unnamed: R1.1, R2.1, U9.4 (X2)
unnamed: R3.1, U9.6 (Y)
OE: U1.119 (IOT34A), U10.19 (~OE)
RAMEN_3V3: U1.38 (IOB8A); also elsewhere on the board
RAS0|RAS_3V3: U1.110 (IOT42B); also elsewhere on the board
RAS1|DRA9_3V3: U1.111 (IOT42A); also elsewhere on the board
READY: RN1.2 (R2.1), U1.22 (IOL14B/READY)
RECONFIG_N: RN1.4 (R4.1), U1.20 (IOL13B/RECONFIG_N)
REGEN_3V3: U1.40 (IOB9A); also elsewhere on the board
RESET_3V3: U1.52 (IOB23A); also elsewhere on the board
RGA1_3V3: U1.51 (IOB17B); also elsewhere on the board
RGA2_3V3: U1.50 (IOB17A); also elsewhere on the board
RGA3_3V3: U1.49 (IOB15B); also elsewhere on the board
RGA4_3V3: U1.48 (IOB15A); also elsewhere on the board
RGA5_3V3: U1.47 (IOB13B); also elsewhere on the board
RGA6_3V3: U1.46 (IOB13A); also elsewhere on the board
RGA7_3V3: U1.45 (IOB12B); also elsewhere on the board
RGA8_3V3: U1.44 (IOB12A); also elsewhere on the board
RW_3V3: U1.41 (IOB9B); also elsewhere on the board
TCK: J2.1, R5.1, U1.14 (IOL11B/TCK)
TDI: J2.3, U1.16 (IOL12B/TDI)
TDO: J2.5, RN2.4 (R4.1), U1.18 (IOL13A/TDO)
TMS: J2.9, U1.13 (IOL11A/TMS)
VCCIO3: C28.2, L1.2, U1.5 (IOL3B), U1.9 (VCCIO3), U1.19 (VCCIO3)
VSYNC_3V3: U1.81 (IOR22B); also elsewhere on the board
WE_3V3: U1.42 (IOB11A); also elsewhere on the board
XCLK|A20_3V3: U1.58 (IOB29A/GCLKT_4); also elsewhere on the board
nNTSC: J2.4, RN2.3 (R3.1), U1.142 (IOT8A)
nNTSC_8372_3V3: RN1.1 (R1.1), U1.24 (IOL16B); also elsewhere on the board

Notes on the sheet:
Optional 28M Oscillator circuit 28.375 MHz PAL or 28.6363 MHz NTSC 3.2mm x 2.5 mm x 0.8 mm Crystal

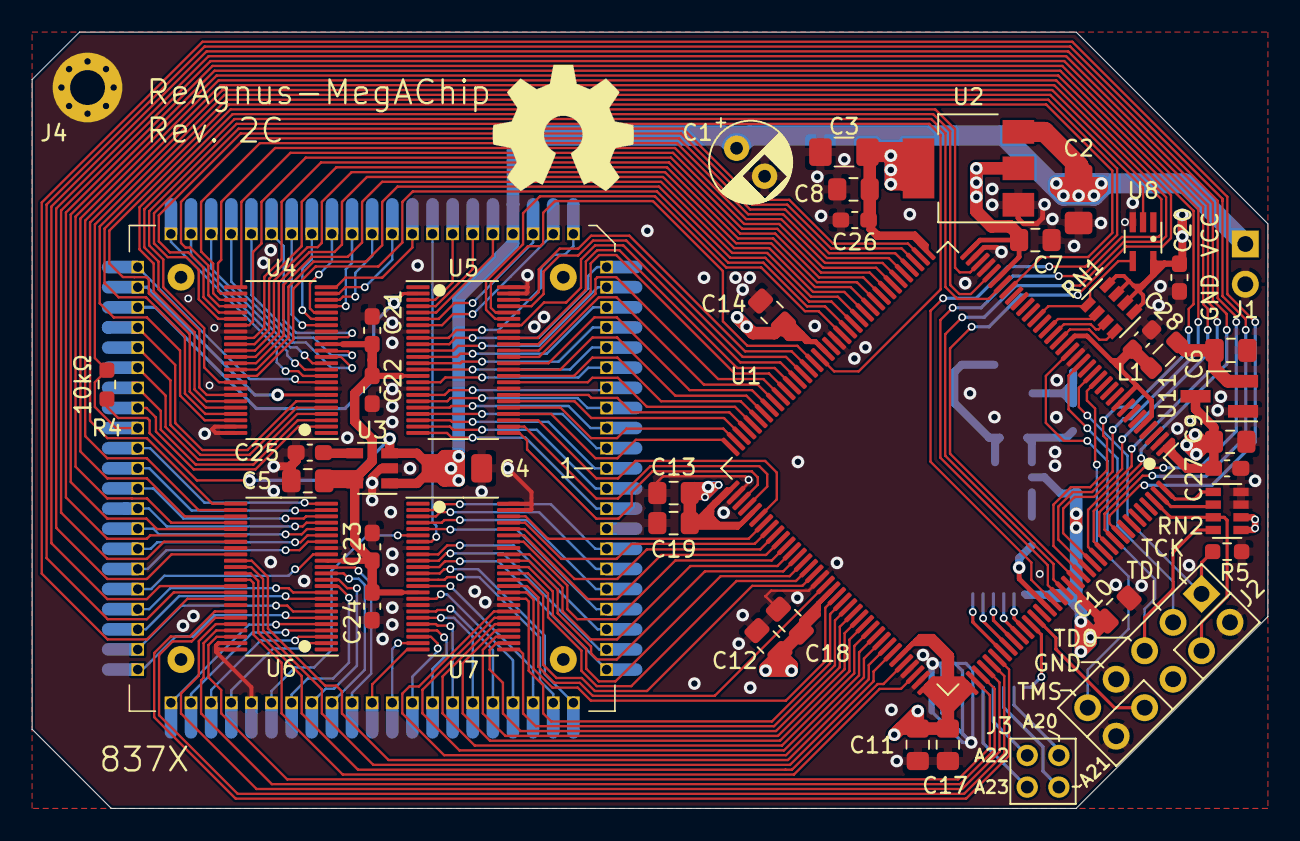
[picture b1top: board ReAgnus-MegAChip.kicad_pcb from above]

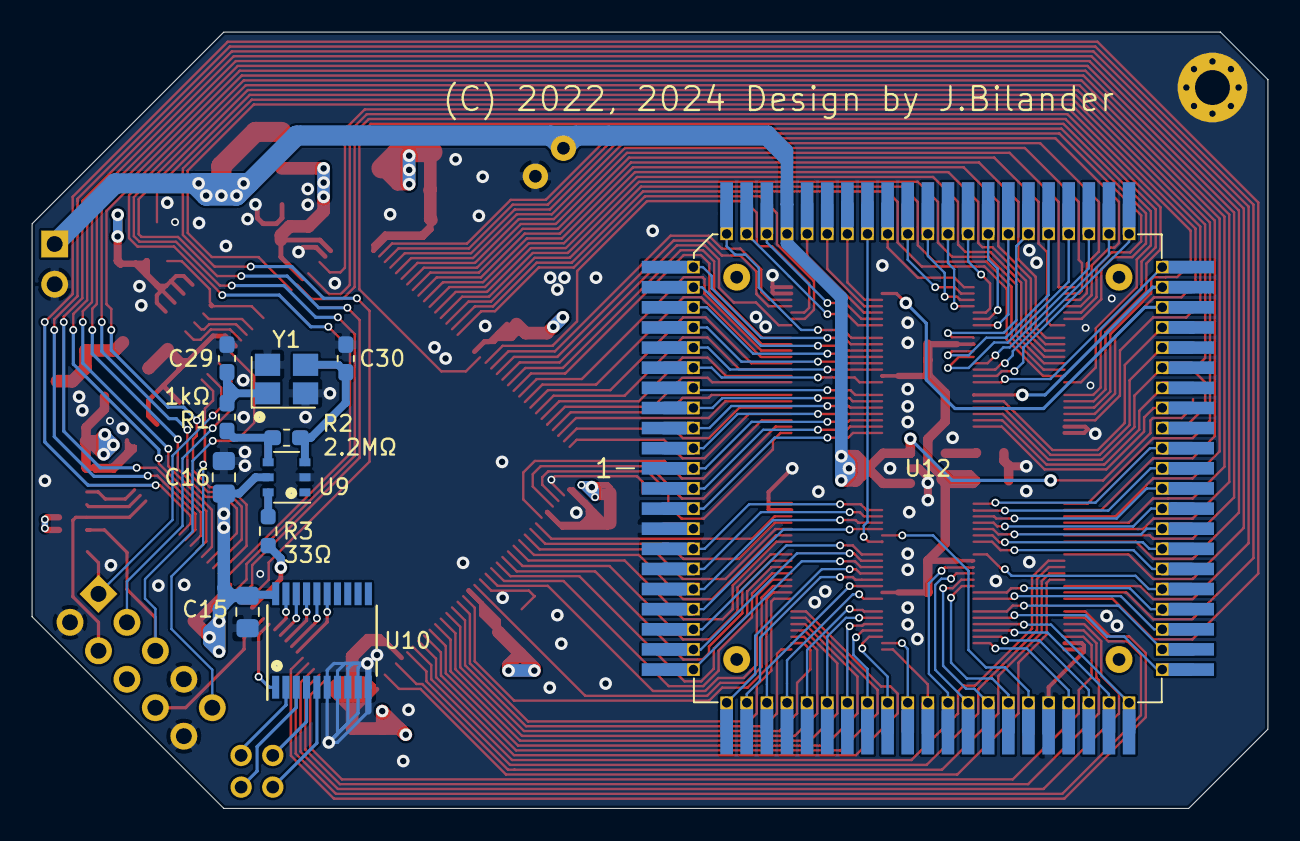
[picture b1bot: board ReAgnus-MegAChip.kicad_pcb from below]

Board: 4 copper layers, 78.0 x 49.0 mm, 56 parts (11 on the bottom side), 195 nets.

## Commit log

2022-08-22 Create LICENSE
2022-08-22 added KiCAD files
2022-08-26 added FPGA schematic file
2022-08-26 more routing and placing components
2022-08-28 made custom footprint
2022-09-01 commit before PCB design change
2022-09-01 major redesign of PCB done
2022-09-02 added footprint
2022-09-02 added 74LVC1G07 buffer with open-drain output
2022-09-03 more routing
2022-09-03 added pull-up resistors on PAL/NTSC-line, added JTAG-header
2022-09-07 fixed routing for VCC to voltage regulator, placed two-pin header for VCC/GND and more routing
2022-09-08 added 3D step file for cay16-103j4lf resistor pack
2022-09-08 went to two layers, deleted inner layers GND and VCC
2022-09-09 renaming of Capacitors
2022-09-14 added Oscillator X1 for SDRAM and GCLKT_1 pin on FPGA
2022-09-15 added 74LVC245A
2022-09-15 added 74LVC245A IC for A20-A23 and more routing done
2022-09-16 added 74LVC1GX04 X-tal driver
2022-09-17 corrected X2-pin to an output on 74LVC1GX04-symbol
2022-09-17 added optional Oscillator circuit with 28M crystal 3.2mm x 2.5mm x 0.8mm
2022-09-22 silkscreen fixes
2022-09-23 added decoupling cap for U11
2022-09-23 fixed power routing and decoupling caps for U10 (SDRAM)
2022-10-05 Added JP3 with pull-up resistor on FPGA-pin IOL5A to J3-jack and changed J3 from a two- to a three-pinHeader.
2022-10-06 via-grounding and silkscreen fixes
2022-10-06 better grounding and silkscreen fixes on backside
2022-10-06 added OSHW silkscreen symbol
2022-10-07 changed to 0.5mm holes (from 0.6mm) due to board house requirement minimum spacing between hole and trace need to be 0.25mm
2022-11-28 Added schematic pdf
2022-11-29 fixed typo XLCK to XCLK on (XCLK/A20) net
2023-01-20 added pics
2023-07-25 footprints fixes
2023-07-25 Changed to 6 mil routing and to updated PLCC-footprint with 0.6mm pinholes and fixed dimensions for homebrew PLCC-84-plug
2023-07-26 Added 3D-models
2023-07-26 Added 3D-model of updated homebrew PLCC-84-plug with pinHeaders mounted
2023-07-26 Added screenshot of 3D-model
2023-07-27 Removed old 3D-models
2023-07-27 Added new 3D-model of homebrew PLCC-84-Plug
2023-07-27 Updated to new 3D-model of homebrew PLCC-84-plug
2024-04-14 Added SN74CBT16210 symbol
2024-04-14 Added more track-width options
2024-04-14 Changed pin-assignment for BLIT_3V3, WE_3V3, RW_3V3 and REGEN_3V3 signals on FPGA to ease routing.
2024-04-14 Changed level shifters from SN74CBTD16210DGGR (TSSOP-48) to SN74CBT16210CDGVR (TVSOP-48) and added a 4.3V LDO regulator TPS73643DBV and re-routed.
2024-04-14 Changed to a four layer stackup, GND and a 3V3 as inner layers, added a MountingHole_2.2mm_M2 for proper grounding via a ring lug connector on a thick jumper wire
2024-04-14 Removed the SDRAM chip and the crystal oscillator
2024-04-18 Went to a 4-layer PCB and changed FPGA to GW1NR-UV9LQ144P with embedded PSRAM, changed FET-bus-switches to SN74CBT16210CDGVR (TVSOP-48) and added 4.3V LDO regulator TPS73643DBV and re-routed.
2024-04-18 Moved signal nNTSC_8372_3V3 to pin FPGA pin 24
2024-04-18 deleted old obsolete schematic
2024-04-18 Added images
2024-05-07 Added a pull-up resistor R4 for pin 41 (PAL/NTSC-selector) because A500 Rev.6A doesn't have pull-up on motherboard, and bumped to Rev. 2B
2024-05-07 Updated schematic pdf
2024-05-08 Updated .gitignore file
2024-05-08 Added .gitignore file
2024-05-08 Add pin-mapping file
2024-05-08 Add gowin project files
2024-05-08 Add main source file
2024-05-08 Added clkdiv2 and clkdiv4 files
2024-05-08 Generating output clocks 14M, 7M, CDAC, CCK and CCKQ
2024-05-12 Moved signals from bank 3 to bank 0
2024-05-12 Assigned DIR-signal to FPGA from U10 (74LVC245)
2024-05-13 Added 1.8V SOT-23 LDO MCP1702T-1802E_CB
2024-05-13 Added LDO MCP1702T-1802E_CB and stacked inductor L1
2024-05-13 Added 1.8V LDO MCP1702T-1802E_CB to feed VCCIO3 (pSRAM) + inductor and decoupling and fixed routing, added pull-up resistor for JTAG TDO
2024-05-13 Bump version to Rev. 2C
2024-05-13 Add schematic pdf
2024-07-04 Changed L1 from inductor to ferrite bead 600 Ohms impedance, changed C6 to 10uF, C9 to 1uF, C27 to 0.1uF, C28 to 0.1uF

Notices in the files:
KiCad/ReAgnus-MegAChip.kicad_pcb:
(C) 2022, 2024 Design by J.Bilander
